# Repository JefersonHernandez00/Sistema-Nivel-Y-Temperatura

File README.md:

# Sistema-Nivel-Y-Temperatura

Electronic project with Arduino, it consists of a level and temperature system for aquifer wells, and shows the data on an LCD and saves them in a micro SD memory

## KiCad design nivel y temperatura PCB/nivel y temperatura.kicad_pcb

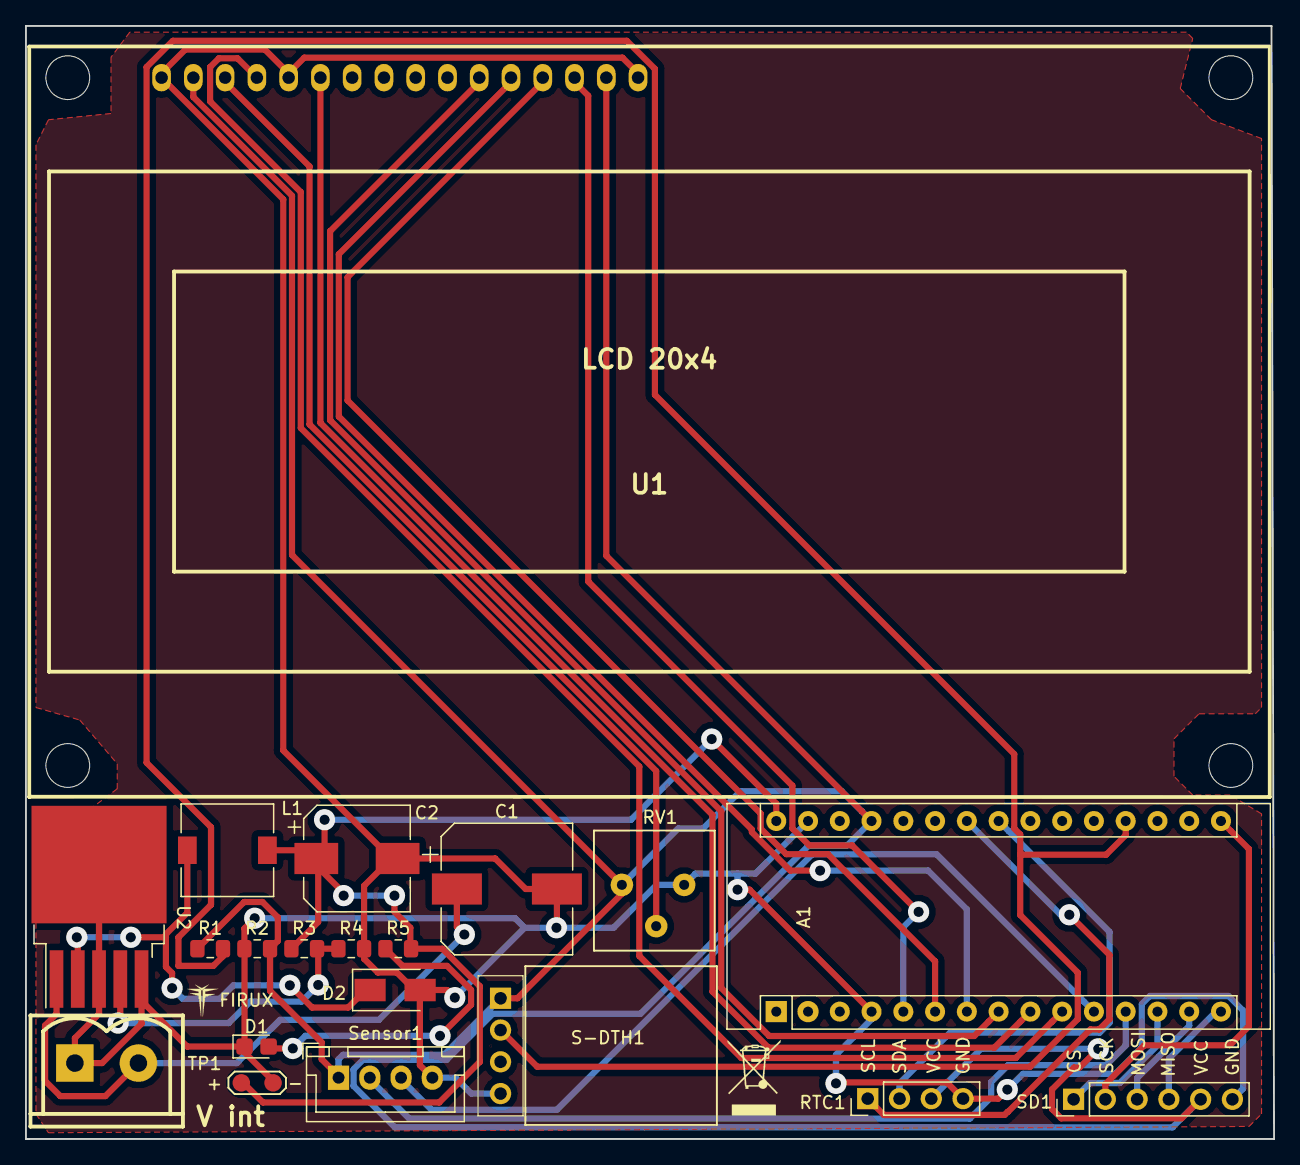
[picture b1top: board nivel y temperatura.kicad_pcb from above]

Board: 2 copper layers, 99.8 x 89.0 mm, 20 parts (0 on the bottom side), 23 nets.

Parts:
 : V int; mstbva_2,5-2-g-5,08
A1: Arduino_Nano
C1: 470uf 35v; CP_Elec_10x10
C2: 220uf 35v; CP_Elec_8x10
D1: LED; LED_0805_2012Metric_Castellated
D2: 1N5825; D_SMA
L1: 68uH; L_7.3x7.3_H4.5
R1, R2: 1k; R_0805_2012Metric_Pad1.15x1.40mm_HandSolder
R3: 6.8K; R_0805_2012Metric_Pad1.15x1.40mm_HandSolder
R4: 1K; R_0805_2012Metric_Pad1.15x1.40mm_HandSolder
R5: 390; R_0805_2012Metric_Pad1.15x1.40mm_HandSolder
RTC1: PinHeader_1x04_P2.54mm_Vertical
RV1: Reostato
S-DTH1: S-DTH-horizontal
SD1: PinHeader_1x06_P2.54mm_Vertical
Sensor1: JST_XH_B04B-XH-A_1x04_P2.50mm_Vertical
TP1: TestPoint_2Pole; TestPoint_2Pads_Pitch2.54mm_Drill0.8mm
U1: LCD 20x4; lcd_20x4
U2: LM2596S-ADJ; TO-263-5_TabPin3

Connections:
+5V: A1.27, R1.1, R2.2, RTC1.3, RV1.2, S-DTH1.1, SD1.5, Sensor1.1, U1.2, U1.15
A0: A1.19, R1.2, S-DTH1.2
A4: A1.23, RTC1.2
A5: A1.24, RTC1.1
D2: A1.5, U1.14
D3: A1.6, U1.13
D4: A1.7, U1.12
D5: A1.8, U1.11
D6: A1.9, U1.6
D7: A1.10, U1.4
D8: A1.11, Sensor1.3
D9: A1.12, Sensor1.2
D10: A1.13, SD1.1
D11: A1.14, SD1.3
D12: A1.15, SD1.4
D13: A1.16, SD1.2
GND: .1, A1.4, A1.29, C1.2, C2.2, D1.1, D2.2, R2.1, R4.2, RTC1.4, RV1.3, S-DTH1.4, SD1.6, Sensor1.4, TP1.2, U1.1, U1.5, U1.16, U2.3, U2.5
unnamed: .2, C1.1, U2.1
unnamed: D1.2, R5.1
unnamed: D2.1, L1.1, U2.2
unnamed: R3.2, R4.1, U2.4
unnamed: RV1.1, U1.3
Vout: A1.30, C2.1, L1.2, R3.1, R5.2, TP1.1

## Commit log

2022-06-05 Electronic project with Arduino, it consists of a level and temperature system for aquifer wells, and shows the data on an LCD and saves them in a micro SD memory
